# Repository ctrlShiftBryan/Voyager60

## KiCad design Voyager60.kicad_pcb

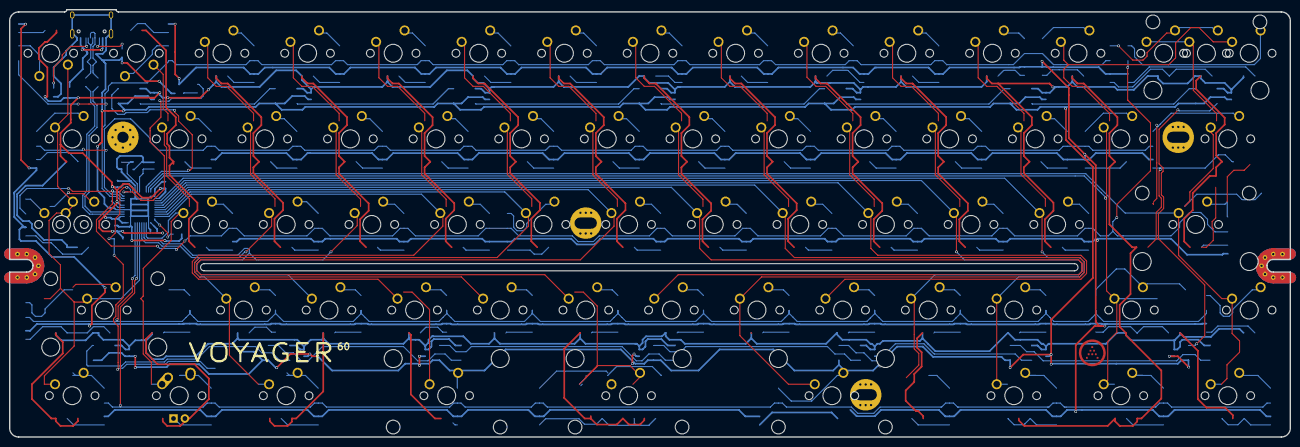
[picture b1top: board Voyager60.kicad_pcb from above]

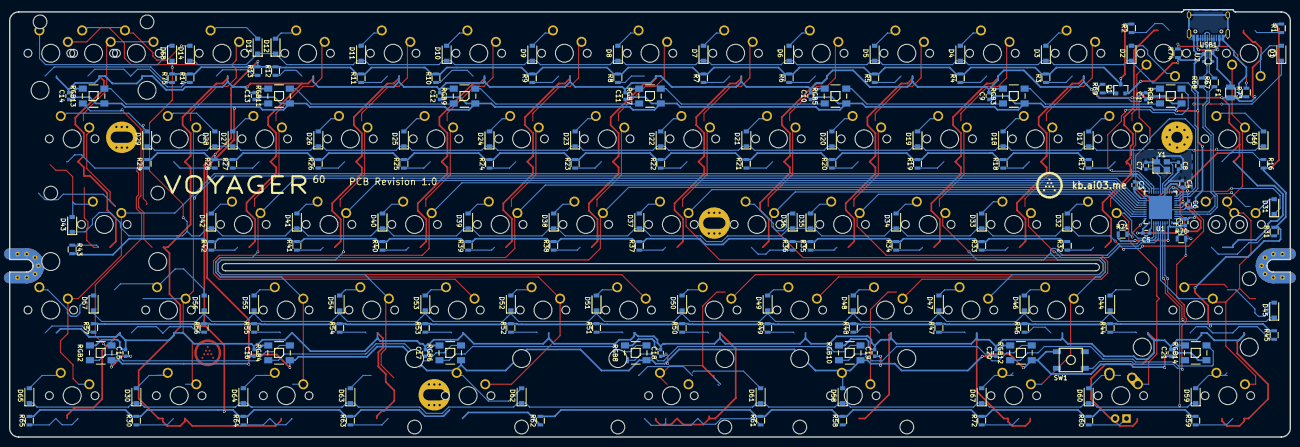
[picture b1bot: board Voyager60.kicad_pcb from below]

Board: 2 copper layers, 285.0 x 95.1 mm, 247 parts (181 on the bottom side), 115 nets.

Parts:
C1, C3, C4, C5, C9, C10, C11, C12, C13, C14, C15, C16, C17, C18, C19, C20, C21: 0.1uF; C_0603
C2: 10uF; C_0603
C6: 1uF; C_0603
C7, C8: 22pF; C_0603
D1, D2, D3, D4, D5, D6, D7, D8, D9, D10, D11, D12, D13, D14, D16, D17, D18, D19, D20, D21, D22, D23, D24, D25, D26, D27, D28, D29, D30, D31, D32, D33, D34, D35, D36, D37, D38, D39, D40, D41, D42, D43, D44, D45, D46, D47, D48, D49, D50, D51, D52, D53, D54, D55, D56, D57, D58, D59, D60, D61, D62, D63, D64, D65, D67, D68: SOD-123; D_SOD-123
F1: 500mA; Fuse_SMD1206_Reflow
K_#1, K_#2, K_#3, K_#4, K_#5, K_#6, K_#7, K_#8, K_#9, K_#10: 1U; MXOnly-1U-NoLED
K_'1: 1U; MXOnly-1U-NoLED
K_,1: 1U; MXOnly-1U-NoLED
K_-1: 1U; MXOnly-1U-NoLED
K_.1: 1U; MXOnly-1U-NoLED
K_/1: 1U; MXOnly-1U-NoLED
K_;1: 1U; MXOnly-1U-NoLED
K_=1: 1U; MXOnly-1U-NoLED
K_A1: 1U; MXOnly-1U-NoLED
K_ALT2: MX-1.5U; MXOnly-1.5U-NoLED
K_B1: 1U; MXOnly-1U-NoLED
K_BACK1: 2U; MXOnly-2U-NoLED
K_C1: 1U; MXOnly-1U-NoLED
K_CAPS1: 1.75U; MXOnly-1.75U-NoLED
K_CAPS2: MX-1.25U; MXOnly-1.25U-NoLED
K_CTRL2: MX-1.5U; MXOnly-1.5U-NoLED
K_D1: 1U; MXOnly-1U-NoLED
K_E1: 1U; MXOnly-1U-NoLED
K_ENTER1: 2.25U; MXOnly-2.25U-NoLED
K_ESC1: 1U; MXOnly-1U-NoLED
K_F1: 1U; MXOnly-1U-NoLED
K_G1: 1U; MXOnly-1U-NoLED
K_H1: 1U; MXOnly-1U-NoLED
K_I1: 1U; MXOnly-1U-NoLED
K_J1: 1U; MXOnly-1U-NoLED
K_K1: 1U; MXOnly-1U-NoLED
K_L1: 1U; MXOnly-1U-NoLED
K_M1: 1U; MXOnly-1U-NoLED
K_N1: 1U; MXOnly-1U-NoLED
K_O1: 1U; MXOnly-1U-NoLED
K_P1: 1U; MXOnly-1U-NoLED
K_Q1: 1U; MXOnly-1U-NoLED
K_R1: 1U; MXOnly-1U-NoLED
K_RALT3: MX-1.5U; MXOnly-1.5U-NoLED
K_RCTRL3: MX-1.5U; MXOnly-1.5U-NoLED
K_RWIN3: 1U; MXOnly-1U-NoLED
K_S1: 1U; MXOnly-1U-NoLED
K_SBACK1, K_SBACK2: 1U; MXOnly-1U-NoLED
K_SHIFT1: 2.25U; MXOnly-2.25U-NoLED
K_SPACE3: MX-2.25U; MXOnly-2.25U-ReversedStabilizers-NoLED
K_SPACE4: MX-2.75U; MXOnly-2.75U-ReversedStabilizers-NoLED
K_SPACE5: 2U; MXOnly-2U-ReversedStabilizers-NoLED
K_SRSHIFT1: 1.75U; MXOnly-1.75U-NoLED
K_SRSHIFT2: 1U; MXOnly-1U-NoLED
K_T1: 1U; MXOnly-1U-NoLED
K_TAB1: 1.5U; MXOnly-1.5U-NoLED
K_U1: 1U; MXOnly-1U-NoLED
K_V1: 1U; MXOnly-1U-NoLED
K_W1: 1U; MXOnly-1U-NoLED
K_WIN2: MX-1U; MX-1U-FLIPPED
K_X1: 1U; MXOnly-1U-NoLED
K_Y1: 1U; MXOnly-1U-NoLED
K_Z1: 1U; MXOnly-1U-NoLED
K_[1: 1U; MXOnly-1U-NoLED
K_\1: 1.5U; MXOnly-1.5U-NoLED
K_]1: 1U; MXOnly-1U-NoLED
Q1: 2N7002; SOT-23
R1, R2, R3, R4, R5, R6, R7, R8, R9, R10, R11, R12, R13, R14, R16, R17, R18, R19, R20, R21, R22, R23, R24, R25, R26, R27, R28, R29, R30, R31, R32, R33, R34, R35, R36, R37, R38, R39, R40, R41, R42, R43, R44, R45, R46, R47, R48, R49, R50, R51, R52, R53, R54, R55, R56, R57, R58, R59, R60, R61, R62, R63, R64, R65, R69, R71, R72, R75: 1k; R_0805
R67, R68: 22; R_0805
R70: 10k; R_0805
R73, R74: 5.1k; R_0805
RGB1, RGB2, RGB3, RGB4, RGB5, RGB6, RGB7, RGB8, RGB9, RGB10, RGB11, RGB12, RGB13, RGB14: WS2812B
SW1: 5.2x5.2mm; SKQG-1155865
U1: ATmega32U4-MU; QFN-44-1EP_7x7mm_Pitch0.5mm
U2: PRTR5V0U2X; SOT143B
USB1: HRO-TYPE-C-31-M-12; HRO-TYPE-C-31-M-12-Assembly
Y1: 16Mhz; Crystal_SMD_3225-4pin_3.2x2.5mm

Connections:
+5V: C1.2, C2.2, C3.2, C4.2, C5.2, C9.2, C10.2, C11.2, C12.2, C13.2, C14.2, C15.2, C16.2, C17.2, C18.2, C19.2, C20.2, C21.2, F1.1, K_WIN2.3, R70.1, RGB1.1, RGB2.1, RGB3.1, RGB4.1, RGB5.1, RGB6.1, RGB7.1, RGB8.1, RGB9.1, RGB10.1, RGB11.1, RGB12.1, RGB13.1, RGB14.1, U1.2, U1.7, U1.14, U1.24, U1.34, U1.44
COL0: K_CAPS1.1, K_CAPS2.2, K_CTRL2.1, K_ESC1.1, K_SHIFT1.1, K_TAB1.1, U1.39
COL1: K_#1.1, K_A1.1, K_Q1.1, K_WIN2.1, U1.36
COL2: K_#2.1, K_ALT2.1, K_S1.1, K_W1.1, K_Z1.1, U1.38
COL3: K_#3.1, K_D1.1, K_E1.1, K_X1.1, U1.37
COL4: K_#4.1, K_C1.1, K_F1.1, K_R1.1, K_SPACE3.1, U1.32
COL5: K_#5.1, K_G1.1, K_T1.1, K_V1.1, U1.31
COL6: K_#6.1, K_B1.1, K_H1.1, K_SPACE5.2, K_Y1.1, U1.30
COL7: K_#7.1, K_J1.1, K_N1.1, K_U1.1, U1.29
COL8: K_#8.1, K_I1.1, K_K1.1, K_M1.1, K_SPACE4.1, U1.28
COL9: K_#9.1, K_,1.1, K_L1.1, K_O1.1, U1.27
COL10: K_#10.1, K_.1.1, K_;1.1, K_P1.1, U1.26
COL11: K_'1.1, K_-1.1, K_/1.1, K_RALT3.1, K_[1.1, U1.25
COL12: K_=1.1, K_RWIN3.1, K_SBACK2.1, K_SRSHIFT1.1, K_]1.1, U1.22
COL13: K_BACK1.1, K_ENTER1.1, K_RCTRL3.1, K_SBACK1.1, K_SRSHIFT2.1, K_\1.1, U1.21
D+: R68.1, U1.4
D-: R67.1, U1.3
GND: C1.1, C2.1, C3.1, C4.1, C5.1, C6.2, C7.2, C8.2, C9.1, C10.1, C11.1, C12.1, C13.1, C14.1, C15.1, C16.1, C17.1, C18.1, C19.1, C20.1, C21.1, Q1.2, R71.1, R73.1, R74.1, RGB1.3, RGB2.3, RGB3.3, RGB4.3, RGB5.3, RGB6.3, RGB7.3, RGB8.3, RGB9.3, RGB10.3, RGB11.3, RGB12.3, RGB13.3, RGB14.3, SW1.1, U1.5, U1.15, U1.23, U1.35, U1.43, U1.45, U2.1, USB1.1, USB1.12, USB1.13, Y1.2, Y1.4
LEDGND: Q1.3, R1.2, R2.2, R3.2, R4.2, R5.2, R6.2, R7.2, R8.2, R9.2, R10.2, R11.2, R12.2, R13.2, R14.2, R16.2, R17.2, R18.2, R19.2, R20.2, R21.2, R22.2, R23.2, R24.2, R25.2, R26.2, R27.2, R28.2, R29.2, R30.2, R31.2, R32.2, R33.2, R34.2, R35.2, R36.2, R37.2, R38.2, R39.2, R40.2, R41.2, R42.2, R43.2, R44.2, R45.2, R46.2, R47.2, R48.2, R49.2, R50.2, R51.2, R52.2, R53.2, R54.2, R55.2, R56.2, R57.2, R58.2, R59.2, R60.2, R61.2, R62.2, R63.2, R64.2, R65.2, R72.2, R75.2
unnamed: C6.1, U1.6
unnamed: C7.1, U1.17, Y1.1
unnamed: C8.1, U1.16, Y1.3
unnamed: D1.2, K_ESC1.2
unnamed: D2.2, K_#1.2
unnamed: D3.2, K_#2.2
unnamed: D4.2, K_#3.2
unnamed: D5.2, K_#4.2
unnamed: D6.2, K_#5.2
unnamed: D7.2, K_#6.2
unnamed: D8.2, K_#7.2
unnamed: D9.2, K_#8.2
unnamed: D10.2, K_#9.2
unnamed: D11.2, K_#10.2
unnamed: D12.2, K_-1.2
unnamed: D13.2, K_=1.2
unnamed: D14.2, K_BACK1.2, K_SBACK1.2
unnamed: D16.2, K_TAB1.2
unnamed: D17.2, K_Q1.2
unnamed: D18.2, K_W1.2
unnamed: D19.2, K_E1.2
unnamed: D20.2, K_R1.2
unnamed: D21.2, K_T1.2
unnamed: D22.2, K_Y1.2
unnamed: D23.2, K_U1.2
unnamed: D24.2, K_I1.2
unnamed: D25.2, K_O1.2
unnamed: D26.2, K_P1.2
unnamed: D27.2, K_[1.2
unnamed: D28.2, K_]1.2
unnamed: D29.2, K_\1.2
unnamed: D30.2, K_RWIN3.2
unnamed: D31.2, K_CAPS1.2, K_CAPS2.1
unnamed: D32.2, K_A1.2
unnamed: D33.2, K_S1.2
unnamed: D34.2, K_D1.2
unnamed: D35.2, K_F1.2
unnamed: D36.2, K_G1.2
unnamed: D37.2, K_H1.2
unnamed: D38.2, K_J1.2
unnamed: D39.2, K_K1.2
unnamed: D40.2, K_L1.2
unnamed: D41.2, K_;1.2
unnamed: D42.2, K_'1.2
unnamed: D43.2, K_ENTER1.2
unnamed: D45.2, K_SHIFT1.2
unnamed: D46.2, K_Z1.2
unnamed: D47.2, K_X1.2
unnamed: D48.2, K_C1.2
unnamed: D49.2, K_V1.2
unnamed: D50.2, K_B1.2
unnamed: D51.2, K_N1.2
unnamed: D52.2, K_M1.2
unnamed: D53.2, K_,1.2
unnamed: D54.2, K_.1.2
unnamed: D55.2, K_/1.2
unnamed: D56.2, K_SRSHIFT1.2
unnamed: D57.2, K_SRSHIFT2.2
unnamed: D58.2, K_SPACE3.2
unnamed: D59.2, K_CTRL2.2
unnamed: D60.2, K_WIN2.2
unnamed: D61.2, K_SPACE5.1
unnamed: D62.2, K_SPACE4.2
unnamed: D64.2, K_RALT3.2
unnamed: D65.2, K_RCTRL3.2
unnamed: D67.2, K_ALT2.2
unnamed: D68.2, K_SBACK2.2
unnamed: K_WIN2.4, R60.1
unnamed: Q1.1, R69.1
unnamed: R67.2, U2.3, USB1.5, USB1.7
unnamed: R68.2, U2.2, USB1.6, USB1.8
unnamed: R69.2, U1.12
unnamed: R70.2, SW1.2, U1.13
unnamed: R71.2, U1.33
unnamed: R73.2, USB1.4
unnamed: R74.2, USB1.10
unnamed: RGB1.2, RGB3.4
unnamed: RGB2.2, RGB4.4
unnamed: RGB3.2, RGB5.4
unnamed: RGB4.2, RGB6.4
unnamed: RGB5.2, RGB7.4
unnamed: RGB6.2, RGB8.4
unnamed: RGB7.2, RGB9.4
unnamed: RGB10.2, RGB12.4
unnamed: RGB8.2, RGB10.4
unnamed: RGB11.2, RGB13.4
unnamed: RGB9.2, RGB11.4
unnamed: RGB12.2, RGB14.4
unnamed: RGB2.4, RGB13.2
RGBLED: RGB1.4, U1.20
ROW0: D1.1, D2.1, D3.1, D4.1, D5.1, D6.1, D7.1, D8.1, D9.1, D10.1, D11.1, D12.1, D13.1, D14.1, U1.9
ROW1: D16.1, D17.1, D18.1, D19.1, D20.1, D21.1, D22.1, D23.1, D24.1, D25.1, D26.1, D27.1, D28.1, D29.1, U1.10
ROW2: D31.1, D32.1, D33.1, D34.1, D35.1, D36.1, D37.1, D38.1, D39.1, D40.1, D41.1, D42.1, D43.1, D68.1, U1.11
ROW3: D44.1, D45.1, D46.1, D47.1, D48.1, D49.1, D50.1, D51.1, D52.1, D53.1, D54.1, D55.1, D56.1, D57.1, U1.41
ROW4: D30.1, D58.1, D59.1, D60.1, D61.1, D62.1, D63.1, D64.1, D65.1, D67.1, U1.40
VCC: F1.2, U2.4, USB1.2, USB1.11

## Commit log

2020-11-08 start changes
2020-11-09 start changing schematic
